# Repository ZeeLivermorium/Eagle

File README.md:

# Eagle Libraries And Projects

Some of my custom Eagle libraries and projects that are probably worth sharing.

- See [libraries](libraries) folder for libraries.
- See [projects](projects) folder for projects.

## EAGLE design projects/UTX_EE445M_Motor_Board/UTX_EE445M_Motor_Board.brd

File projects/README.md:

# Eagle Projects
Some of my Eagle project files.

## [ESP8266 Programmer](ESP8266_Programmer)
A firmware programmer of ESP8266-01 wifi module. You can also use it for serial input for your ESP8266.

## [NFC Demo Board - PN532 - TM4C123GXL](LiDAR_Demo_Board-VL53L0X-TM4C123G)
A demo board for NFC functionality demo, utilizing NXP PN532 NXP Controller and TI TM4C123GXL MCU.

## [LiDAR Demo Board - VL53L0X - TM4C123GXL](LiDAR_Demo_Board_Vert-VL53L0X-TM4C123G)
A demo board for STMicroeletronics VL53L0X ToF LiDAR sensor with TI TM4C123GXL MCU.

## [LiDAR Demo Board Vertical - VL53L0X - TM4C123GXL](NFC_Demo_Board-PN532-TM4C123G)
Another version of the LiDAR demo board with the LiDAR sensor standing vertically.

## [UTexas EE445M Front LiDAR Board Version 1](UTX_EE445M_Front_LiDAR_Board_1)
A PCB for holding front LiDAR sensors for UTexas EE445M autonomous driving car.

## [UTexas EE445M Front LiDAR Board Version 2](UTX_EE445M_Front_LiDAR_Board_2)
Another version of LiDAR front board for easier custom placement for LiDAR sensors.

## [ICDI Debugger Bridge](ICDI_Bridge)
A tiny ICDI debugger bridge to debug Tiva MCUs for custom designs.

## [Raspberry Pi Bridge](Raspberry_Pi_Bridge)
A bridge to interface raspberry pi with custom PCBs.

## [LM2596S Buck Converter Reference Board](Buck_Converter_Reference_Board_5V_3A_LM2596S)
A buck converter reference design for LM2596S.

## [UTexas EE445M Sensor Board](UTX_EE445M_Sensor_Board)
My custom sensor board design for my autonomous driving car for UTexas EE445M.

## [UTexas EE445M Motor Board](UTX_EE445M_Motor_Board)
My custom motor board design for my autonomous driving car for UTexas EE445M.

## Copyright Note
Some of the projects here contain Texas Longhorns or UT ECE logos. Those are properties of University of Texas at Austin. Any PCBs that I put those logos on are purely for academic use at UT ECE. If you download my designs from this repo for your personal use, you might want to remove these logos in case UT lawyers call you up to have a cup of tea.

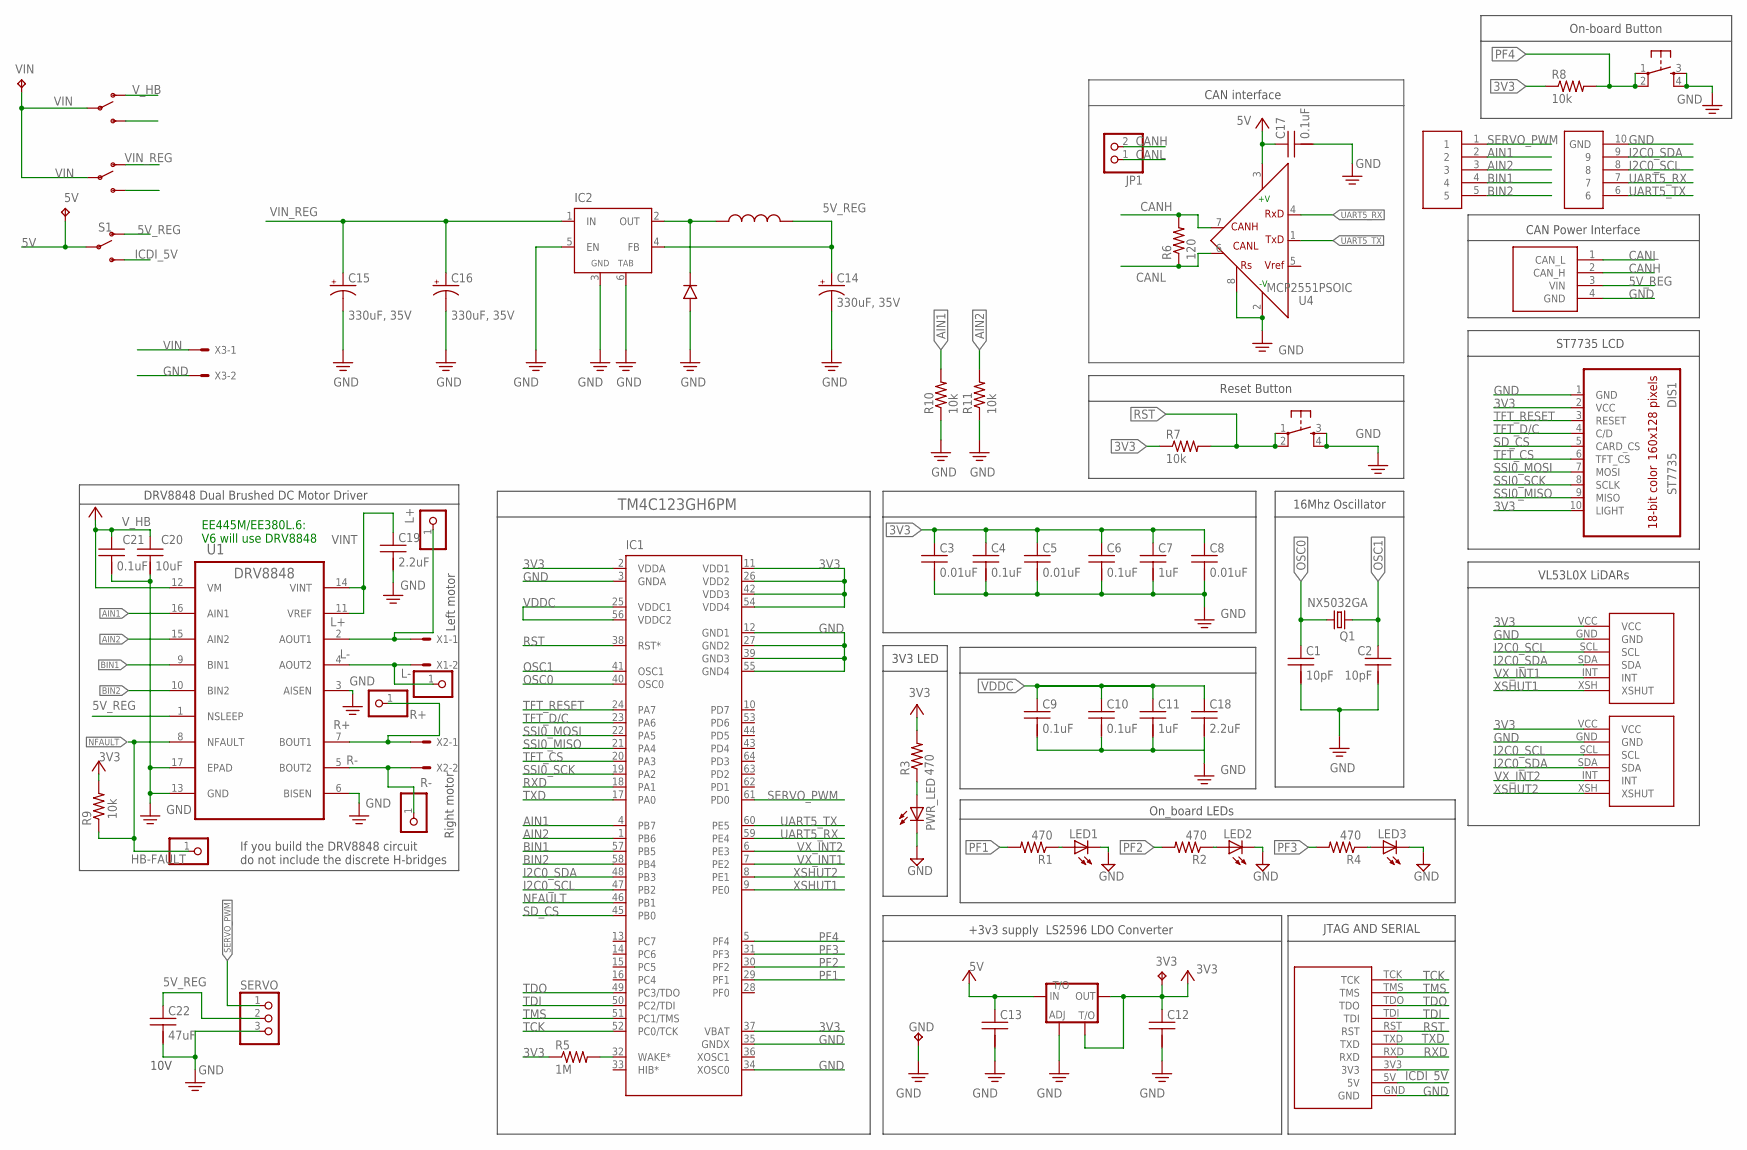
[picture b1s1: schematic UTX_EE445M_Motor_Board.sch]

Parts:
3V3, 5V: TPPAD1-13; P1-13
BUTTON: _SWITCH_DTSM-6
C1, C2: 10pF; C0603K
C3, C5, C8: 0.01uF; C0603K
C4, C6, C9, C10, C17, C21: 0.1uF; C0603K
C7, C11: 1uF; C0603K
C12: CAPACITORC0805K; C0805K
C13: CAPACITORC0603K; C0603K
C14, C15, C16: 330uF, 35V; _CAPACITOR_CHEMI-CON_A_HA0_SMD
C18, C19: 2.2uF; C0603K
C20: 10uF; C0805K
C22: 47uF; C0805K
DIS1: ST7735
GND: TPPAD1-13; P1-13
HB-FAULT: PINHD-1X1; 1X01
IC1: TM4C123GH6PM; SQFP-S-10X10-64
IC2: _VOLTAG_REGULATOR_LM2596S; _PACKAGE_TO263-5
JP1: PINHD-1X2; 1X02
L+: PINHD-1X1; 1X01
L-: PINHD-1X1; 1X01
LED1, LED2, LED3: LEDCHIP-LED0603; CHIP-LED0603
PWR_LED: LEDCHIP-LED0603; CHIP-LED0603
Q1: NX5032GA
R1, R2, R3, R4: 470; R0603
R5: 1M; R0603
R6: 120; R0603
R7, R8, R9, R10, R11: 10k; R0603
R+: PINHD-1X1; 1X01
R-: PINHD-1X1; 1X01
RESET: _SWITCH_DTSM-6
S1: SWITCH-SPDT-PTH-11.6X4.0MM; SWITCH_SPDT_PTH_11.6X4.0MM
SERVO: PINHD-1X3; 1X03
U1: DRV8848; SOP65P640X120-17N
U4: MCP2551PSOIC; SO08
U$1: JTAG_SERIAL; JTAG_SERIAL_PTH
U$2, U$3: LIDAR_VL53L0X_ATK_VERT
U$4, U$5: _SWITCH_SPDT_4.7
U$9: _VOLTAGE_REGULATOR_AMS1117; _PACKAGE_SOT223
U$10: UTX_EE445M_BOARD_CONNECTOR; _HEADER_2_4X1_ANGLED
U$11: LOGIC_ANALYZER_10PIN
U$23: _INDUCTOR_PE-54040SNL; _PACKAGE_HCI-68
U$24: _DIODE_SOD128; _PACKAGE_SOD128
VIN: TPPAD1-13; P1-13
X1, X2, X3: KK-156-2

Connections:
3V3: 3V3.TP, C3.1, C4.1, C5.1, C6.1, C7.1, C8.1, C12.1, DIS1.2 (VCC), DIS1.10 (LIGHT), IC1.2 (VDDA), IC1.11 (VDD1), IC1.26 (VDD2), IC1.37 (VBAT), IC1.42 (VDD3), IC1.54 (VDD4), R3.2, R5.1, R7.1, R8.1, R9.2, U$2.VCC, U$3.VCC, U$9.2 (OUT), U$9.4 (T/O)
5V: 5V.TP, C13.1, C17.1, S1.2, U4.3 (VDD), U$9.3 (IN)
5V_REG: C14.+, C22.1, IC2.4 (FB), S1.1 (O), SERVO.2, U1.1 (NSLEEP), U$10.3 (VIN), U$23.2
AIN1: IC1.4 (PB7), R10.2, U1.16 (AIN1), U$11.2
AIN2: IC1.1 (PB6), R11.2, U1.15 (AIN2), U$11.3
BIN1: IC1.57 (PB5), U1.9 (BIN1), U$11.4
BIN2: IC1.58 (PB4), U1.10 (BIN2), U$11.5
CANH: JP1.2, R6.2, U4.7 (CANH), U$10.2 (CAN_H)
CANL: JP1.1, R6.1, U4.6 (CANL), U$10.1 (CAN_L)
GND: BUTTON.3, BUTTON.4, C1.2, C2.2, C3.2, C4.2, C5.2, C6.2, C7.2, C8.2, C9.2, C10.2, C11.2, C12.2, C13.2, C14.-, C15.-, C16.-, C17.2, C18.2, C19.2, C20.2, C21.2, C22.2, DIS1.1 (GND), GND.TP, IC1.3 (GNDA), IC1.12 (GND1), IC1.27 (GND2), IC1.34 (XOSC0), IC1.35 (GNDX), IC1.39 (GND3), IC1.55 (GND4), IC2.3 (GND), IC2.5 (EN), IC2.6 (TAB), LED1.C, LED2.C, LED3.C, PWR_LED.C, R10.1, R11.1, RESET.3, RESET.4, SERVO.3, U1.3 (AISEN), U1.6 (BISEN), U1.13 (GND), U1.17 (EPAD), U4.2 (VSS), U4.8 (RS), U$1.GND, U$2.GND, U$3.GND, U$9.1 (ADJ), U$10.4 (GND), U$11.10 (GND), U$24.A (+), X3.2
I2C0_SCL: IC1.47 (PB2), U$2.SCL, U$3.SCL, U$11.8
I2C0_SDA: IC1.48 (PB3), U$2.SDA, U$3.SDA, U$11.9
ICDI_5V: S1.3 (S), U$1.5V
L+: L+.1, U1.2 (AOUT1), X1.1
L-: L-.1, U1.4 (AOUT2), X1.2
unnamed: LED1.A, R1.1
unnamed: PWR_LED.A, R3.1
unnamed: LED2.A, R2.1
unnamed: LED3.A, R4.1
unnamed: IC2.2 (OUT), U$23.1, U$24.C (-)
unnamed: IC1.32 (WAKE*), R5.2
NFAULT: HB-FAULT.1, IC1.46 (PB1), R9.1, U1.8 (NFAULT)
OSC0: C1.1, IC1.40 (OSC0), Q1.1
OSC1: C2.1, IC1.41 (OSC1), Q1.2
PF1: IC1.29 (PF1), R1.2
PF2: IC1.30 (PF2), R2.2
PF3: IC1.31 (PF3), R4.2
PF4: BUTTON.1, BUTTON.2, IC1.5 (PF4), R8.2
R+: R+.1, U1.7 (BOUT1), X2.1
R-: R-.1, U1.5 (BOUT2), X2.2
RST: IC1.38 (RST*), R7.2, RESET.1, RESET.2, U$1.RST
RXD: IC1.18 (PA1), U$1.RXD
SD_CS: DIS1.5 (CARD_CS), IC1.45 (PB0)
SERVO_PWM: IC1.61 (PD0), SERVO.1, U$11.1
SSI0_MISO: DIS1.9 (MISO), IC1.21 (PA4)
SSI0_MOSI: DIS1.7 (MOSI), IC1.22 (PA5)
SSI0_SCK: DIS1.8 (SCLK), IC1.19 (PA2)
TCK: IC1.52 (PC0/TCK), U$1.TCK
TDI: IC1.50 (PC2/TDI), U$1.TDI
TDO: IC1.49 (PC3/TDO), U$1.TDO
TFT_CS: DIS1.6 (TFT_CS), IC1.20 (PA3)
TFT_D/C: DIS1.4 (C/D), IC1.23 (PA6)
TFT_RESET: DIS1.3 (RESET), IC1.24 (PA7)
TMS: IC1.51 (PC1/TMS), U$1.TMS
TXD: IC1.17 (PA0), U$1.TXD
UART5_RX: IC1.59 (PE4), U4.4 (RXD), U$11.7
UART5_TX: IC1.60 (PE5), U4.1 (TXD), U$11.6
VDDC: C9.1, C10.1, C11.1, C18.1, IC1.25 (VDDC1), IC1.56 (VDDC2)
VIN: U$4.P$2, U$5.P$2, VIN.TP, X3.1
VINT: C19.1, U1.11 (VREF), U1.14 (VINT)
VIN_REG: C15.+, C16.+, IC2.1 (IN), U$5.P$1 (O)
VX_INT1: IC1.7 (PE2), U$2.INT
VX_INT2: IC1.6 (PE3), U$3.INT
V_HB: C20.1, C21.1, U1.12 (VM), U$4.P$1 (O)
XSHUT1: IC1.9 (PE0), U$2.XSH (XSHUT)
XSHUT2: IC1.8 (PE1), U$3.XSH (XSHUT)

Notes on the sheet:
16Mhz Oscillator
ST7735 LCD
VL53L0X LiDARs
CAN interface
+3v3 supply LS2596 LDO Converter
JTAG AND SERIAL
3V3 LED
On_board LEDs
Reset Button
CAN Power Interface
On-board Button
Left motor
Right motor
DRV8848 Dual Brushed DC Motor Driver
If you build the DRV8848 circuit do not include the discrete H-bridges
EE445M/EE380L.6: V6 will use DRV8848
10V

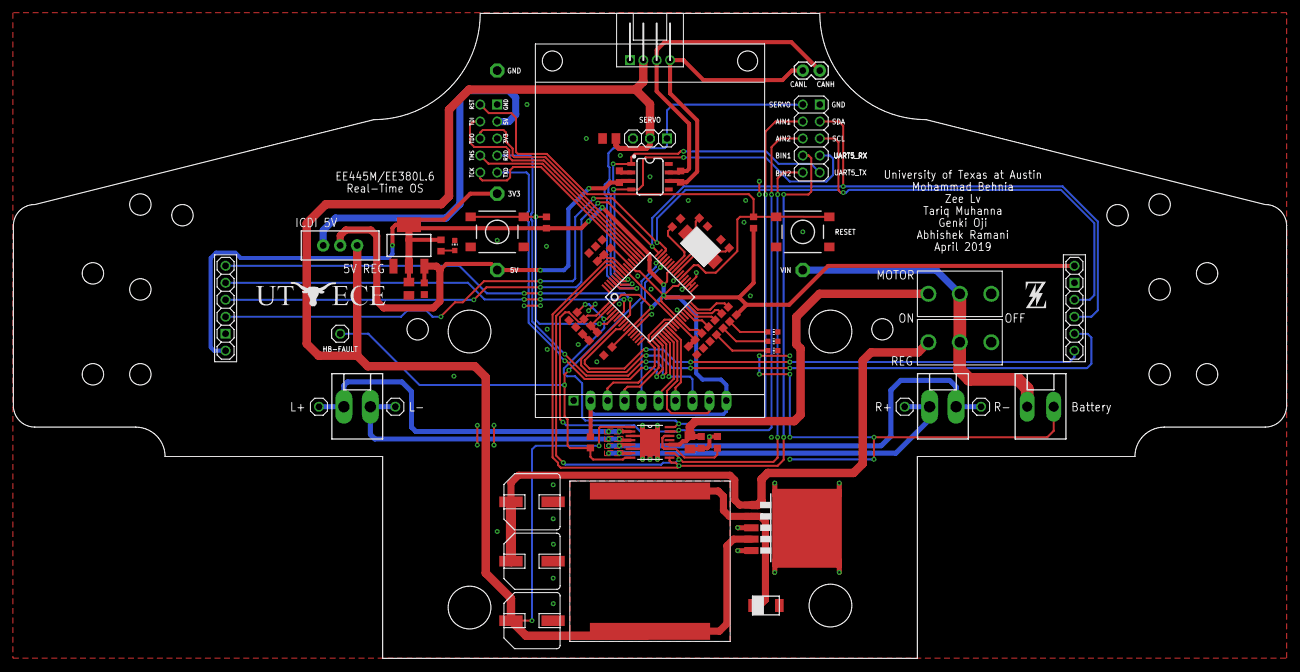
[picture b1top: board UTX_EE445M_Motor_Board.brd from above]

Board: 2 copper layers, 190.5 x 96.5 mm, 72 parts (0 on the bottom side), 56 nets.

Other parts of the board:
U$6: __LOGO_UT_ECE
U$7: __LOGO_Z

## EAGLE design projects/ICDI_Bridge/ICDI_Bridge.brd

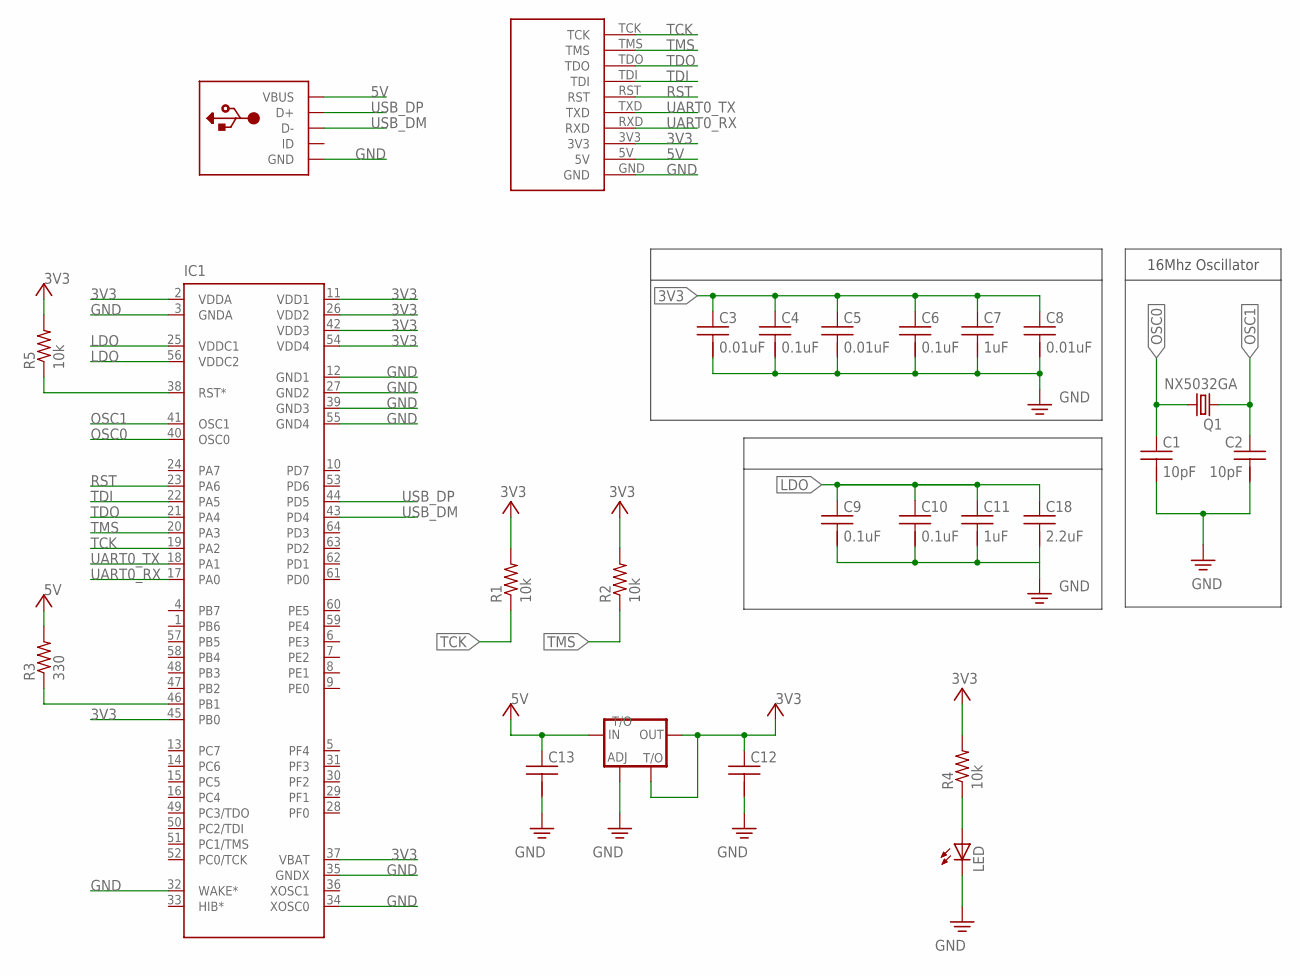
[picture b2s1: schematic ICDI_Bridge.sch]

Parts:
C1, C2: 10pF; C0603K
C3, C5, C8: 0.01uF; C0603K
C4, C6, C9, C10: 0.1uF; C0603K
C7, C11: 1uF; C0603K
C12: CAPACITORC0805K; C0805K
C13: CAPACITORC0603K; C0603K
C18: 2.2uF; C0603K
IC1: TM4C123GH6PM; SQFP-S-10X10-64
LED: LEDCHIPLED_0603; CHIPLED_0603
Q1: NX5032GA
R1, R2, R4, R5: 10k; R0603
R3: 330; R0603
U$1: USB_MICRO_PTH
U$2: JTAG_SERIAL; JTAG_SERIAL_PTH
U$4: _VOLTAGE_REGULATOR_AMS1117; _PACKAGE_SOT223

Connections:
3V3: C3.1, C4.1, C5.1, C6.1, C7.1, C8.1, C12.1, IC1.2 (VDDA), IC1.11 (VDD1), IC1.26 (VDD2), IC1.37 (VBAT), IC1.42 (VDD3), IC1.45 (PB0), IC1.54 (VDD4), R1.2, R2.2, R4.2, R5.2, U$2.3V3, U$4.2 (OUT), U$4.4 (T/O)
5V: C13.1, R3.2, U$1.1 (VBUS), U$2.5V, U$4.3 (IN)
GND: C1.2, C2.2, C3.2, C4.2, C5.2, C6.2, C7.2, C8.2, C9.2, C10.2, C11.2, C12.2, C13.2, C18.2, IC1.3 (GNDA), IC1.12 (GND1), IC1.27 (GND2), IC1.32 (WAKE*), IC1.34 (XOSC0), IC1.35 (GNDX), IC1.39 (GND3), IC1.55 (GND4), LED.C, U$1.5 (GND), U$2.GND, U$4.1 (ADJ)
LDO: C9.1, C10.1, C11.1, C18.1, IC1.25 (VDDC1), IC1.56 (VDDC2)
unnamed: LED.A, R4.1
unnamed: IC1.46 (PB1), R3.1
unnamed: IC1.38 (RST*), R5.1
OSC0: C1.1, IC1.40 (OSC0), Q1.1
OSC1: C2.1, IC1.41 (OSC1), Q1.2
RST: IC1.23 (PA6), U$2.RST
TCK: IC1.19 (PA2), R1.1, U$2.TCK
TDI: IC1.22 (PA5), U$2.TDI
TDO: IC1.21 (PA4), U$2.TDO
TMS: IC1.20 (PA3), R2.1, U$2.TMS
UART0_RX: IC1.17 (PA0), U$2.RXD
UART0_TX: IC1.18 (PA1), U$2.TXD
USB_DM: IC1.43 (PD4), U$1.2 (D-)
USB_DP: IC1.44 (PD5), U$1.3 (D+)

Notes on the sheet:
16Mhz Oscillator

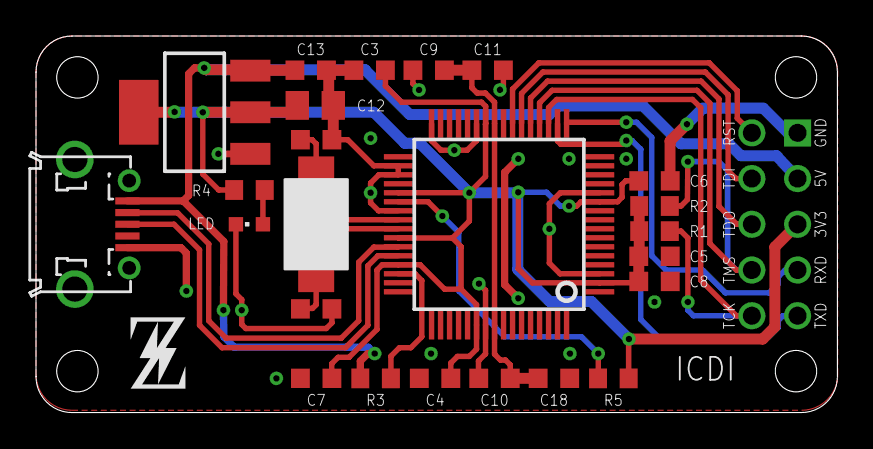
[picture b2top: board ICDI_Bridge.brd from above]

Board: 2 copper layers, 44.5 x 20.9 mm, 26 parts (0 on the bottom side), 18 nets.

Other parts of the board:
U$3: __LOGO_Z

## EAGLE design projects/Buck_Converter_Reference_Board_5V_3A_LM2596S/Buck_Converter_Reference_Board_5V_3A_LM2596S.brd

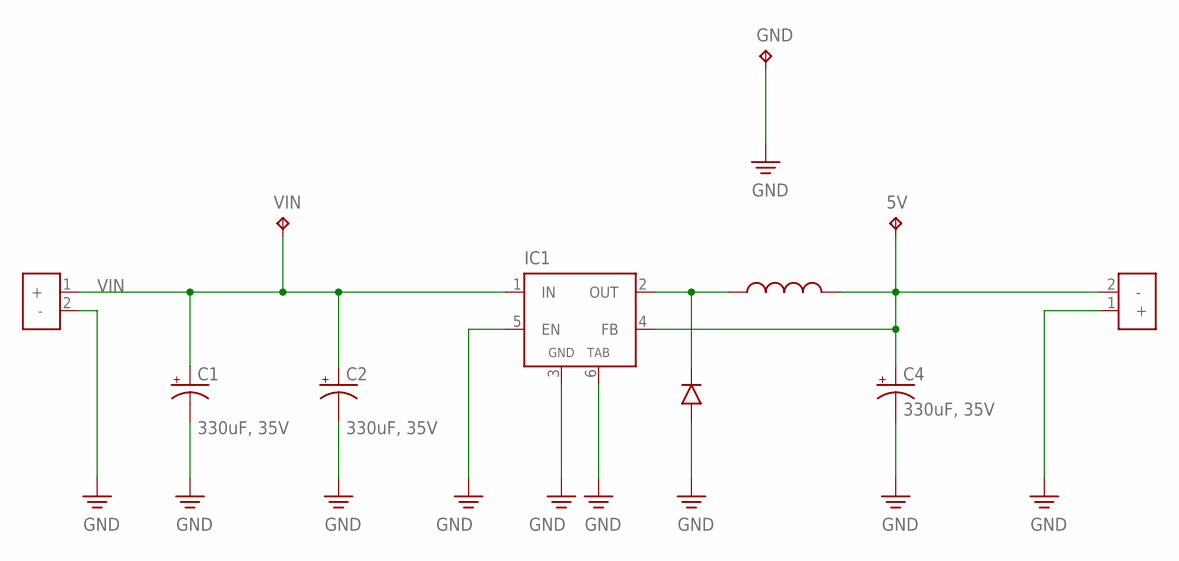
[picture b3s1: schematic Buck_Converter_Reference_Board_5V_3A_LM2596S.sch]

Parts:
5V: TPPAD1-13; P1-13
C1, C2, C4: 330uF, 35V; _CAPACITOR_CHEMI-CON_A_HA0_SMD
GND: TPPAD1-13; P1-13
IC1: _VOLTAG_REGULATOR_LM2596S; _PACKAGE_TO263-5
U$1, U$22: POWER_CONNECTOR; _TERMINAL_BLOCK_2.54_1X2
U$23: _INDUCTOR_PE-54040SNL; _PACKAGE_HCI-68
U$24: _DIODE_SOD128; _PACKAGE_SOD128
VIN: TPPAD1-13; P1-13

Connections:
5V: 5V.TP, C4.+, IC1.4 (FB), U$1.2 (-), U$23.2
GND: C1.-, C2.-, C4.-, GND.TP, IC1.3 (GND), IC1.5 (EN), IC1.6 (TAB), U$1.1 (+), U$22.2 (-), U$24.A (+)
unnamed: IC1.2 (OUT), U$23.1, U$24.C (-)
VIN: C1.+, C2.+, IC1.1 (IN), U$22.1 (+), VIN.TP

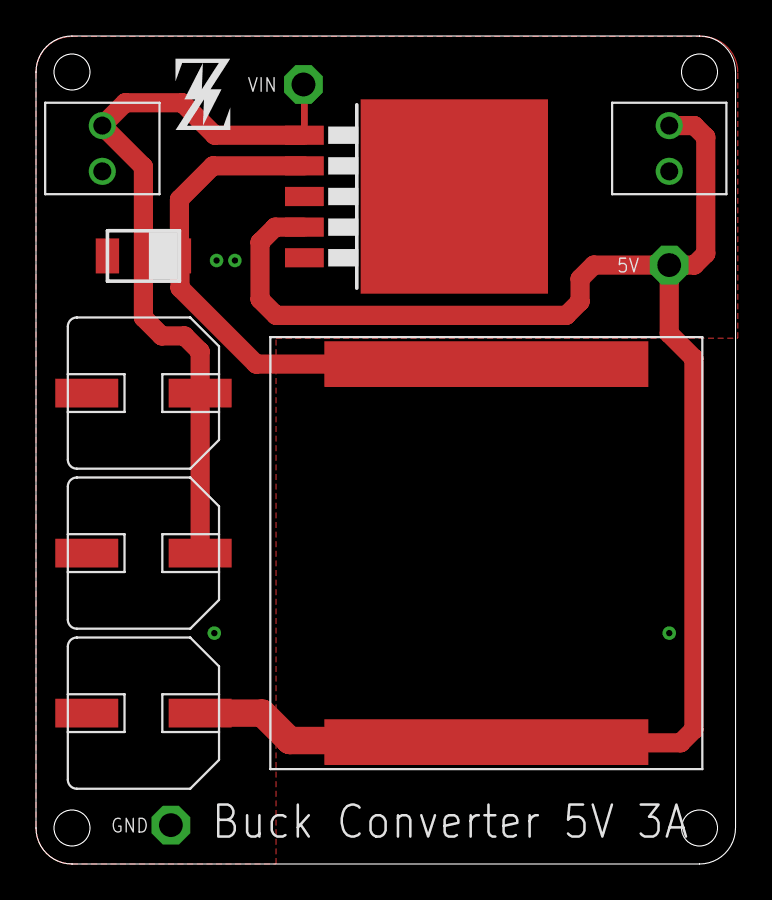
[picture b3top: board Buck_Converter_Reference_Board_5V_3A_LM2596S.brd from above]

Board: 2 copper layers, 38.9 x 46.0 mm, 12 parts (0 on the bottom side), 4 nets.

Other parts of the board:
U$2: __LOGO_Z

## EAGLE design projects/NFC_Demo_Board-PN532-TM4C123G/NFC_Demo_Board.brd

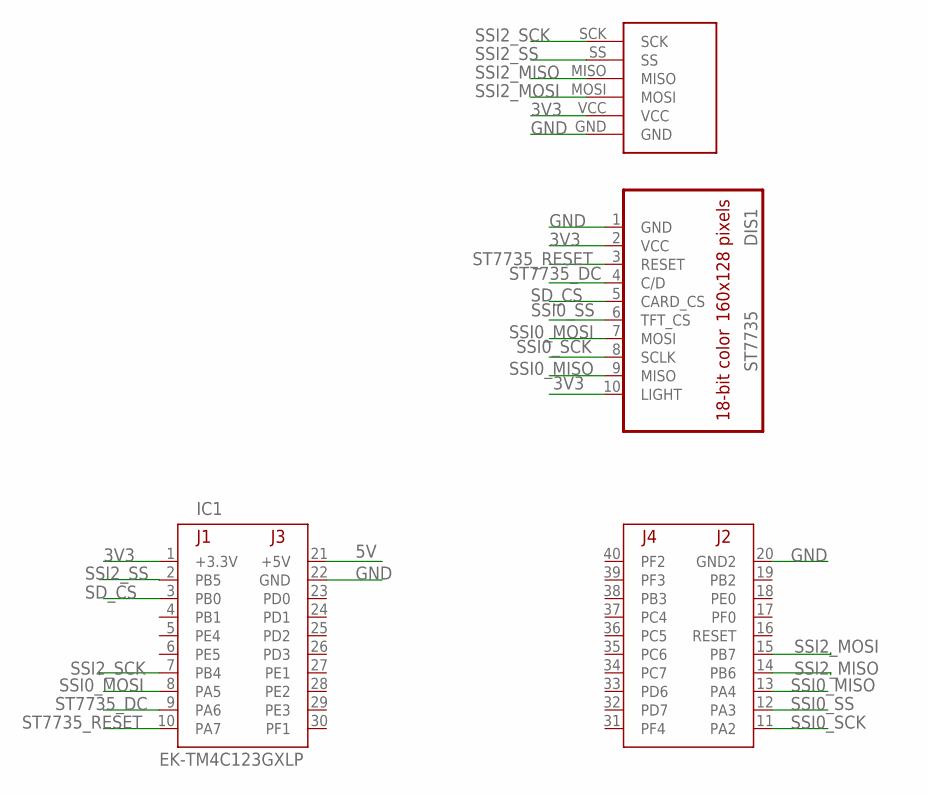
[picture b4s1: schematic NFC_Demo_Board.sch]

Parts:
DIS1: ST7735
IC1: EK-TM4C123GXLP; TM4C123LAUNCHPAD
U$1: ELECHOUSE_PN532_SPI

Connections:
3V3: DIS1.2 (VCC), DIS1.10 (LIGHT), IC1.1 (+3.3V), U$1.VCC
5V: IC1.21 (+5V)
GND: DIS1.1 (GND), IC1.20 (GND2), IC1.22 (GND), U$1.GND
SD_CS: DIS1.5 (CARD_CS), IC1.3 (PB0)
SSI0_MISO: DIS1.9 (MISO), IC1.13 (PA4)
SSI0_MOSI: DIS1.7 (MOSI), IC1.8 (PA5)
SSI0_SCK: DIS1.8 (SCLK), IC1.11 (PA2)
SSI0_SS: DIS1.6 (TFT_CS), IC1.12 (PA3)
SSI2_MISO: IC1.14 (PB6), U$1.MISO
SSI2_MOSI: IC1.15 (PB7), U$1.MOSI
SSI2_SCK: IC1.7 (PB4), U$1.SCK
SSI2_SS: IC1.2 (PB5), U$1.SS
ST7735_DC: DIS1.4 (C/D), IC1.9 (PA6)
ST7735_RESET: DIS1.3 (RESET), IC1.10 (PA7)

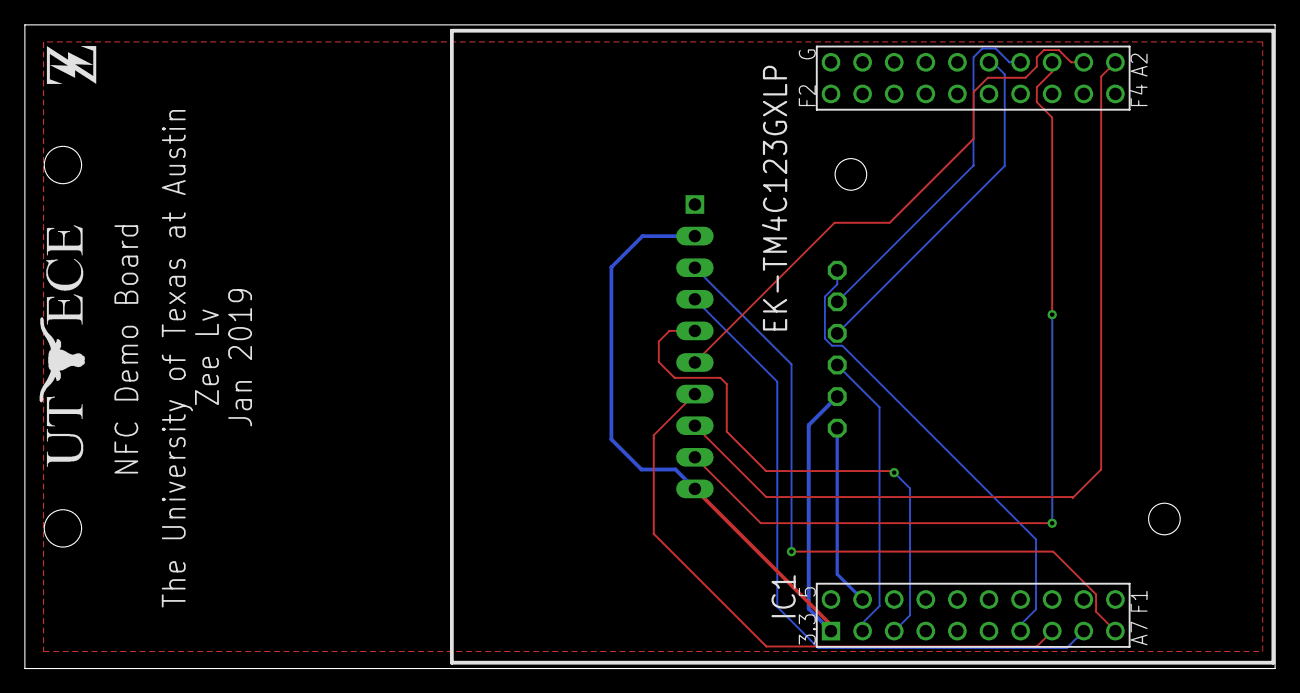
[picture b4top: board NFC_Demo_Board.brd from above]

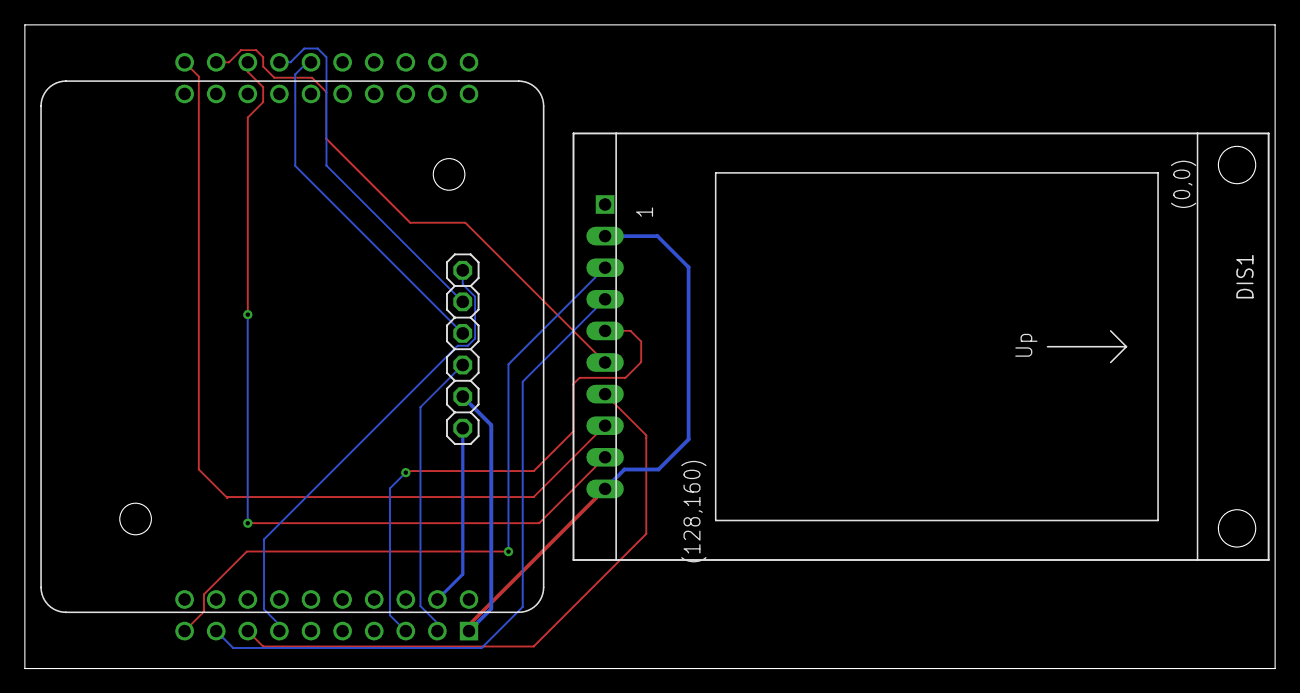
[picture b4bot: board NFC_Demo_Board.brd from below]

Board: 2 copper layers, 100.5 x 51.7 mm, 5 parts (2 on the bottom side), 13 nets.

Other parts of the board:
U$2: LOGO_UT_ECE_20X4
U$3: LOGO_Z_3X4

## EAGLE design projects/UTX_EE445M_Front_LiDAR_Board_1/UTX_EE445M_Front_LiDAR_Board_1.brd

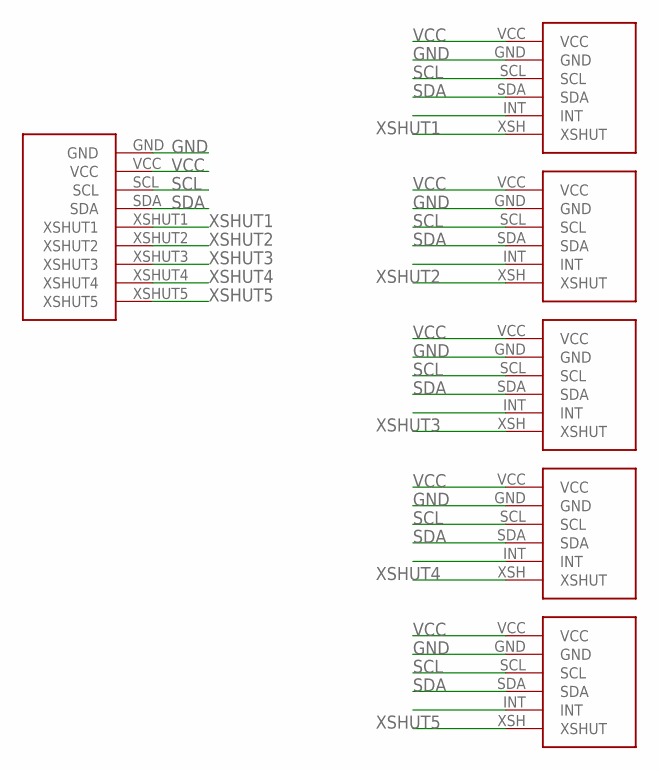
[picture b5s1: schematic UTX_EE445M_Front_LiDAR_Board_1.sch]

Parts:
U$1: UTX_EE445M_LIDAR_FRONT_BOARD_CONNECTOR_PTH
U$2, U$3, U$4, U$5, U$6: LIDAR_VL53L0X_ATK_VERT

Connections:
GND: U$1.GND, U$2.GND, U$3.GND, U$4.GND, U$5.GND, U$6.GND
SCL: U$1.SCL, U$2.SCL, U$3.SCL, U$4.SCL, U$5.SCL, U$6.SCL
SDA: U$1.SDA, U$2.SDA, U$3.SDA, U$4.SDA, U$5.SDA, U$6.SDA
VCC: U$1.VCC, U$2.VCC, U$3.VCC, U$4.VCC, U$5.VCC, U$6.VCC
XSHUT1: U$1.XSHUT1, U$2.XSH (XSHUT)
XSHUT2: U$1.XSHUT2, U$3.XSH (XSHUT)
XSHUT3: U$1.XSHUT3, U$4.XSH (XSHUT)
XSHUT4: U$1.XSHUT4, U$5.XSH (XSHUT)
XSHUT5: U$1.XSHUT5, U$6.XSH (XSHUT)

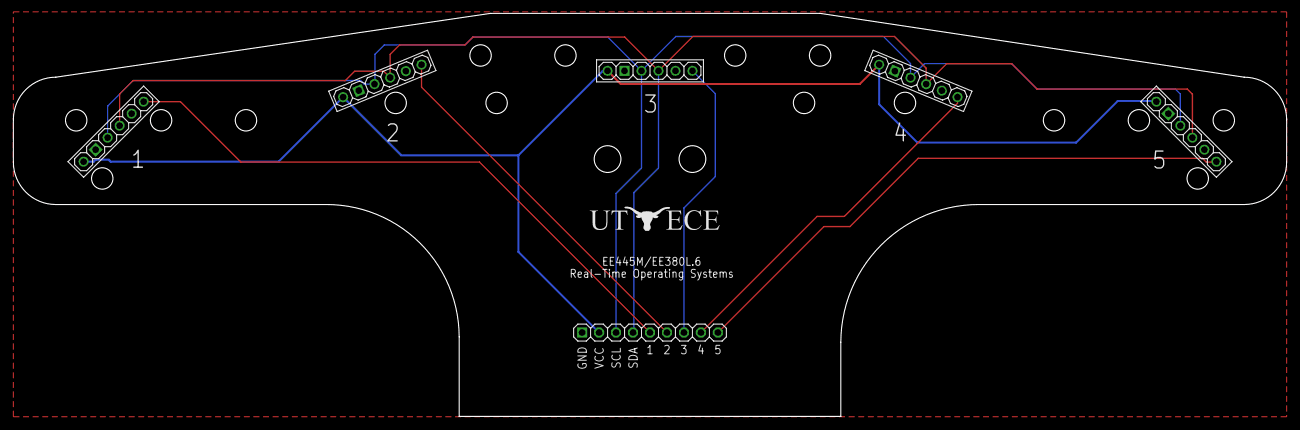
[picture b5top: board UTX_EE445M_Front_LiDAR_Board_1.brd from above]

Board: 2 copper layers, 190.5 x 60.3 mm, 8 parts (1 on the bottom side), 9 nets.

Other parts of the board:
U$7: LOGO_UT_ECE_20X4
U$8: LOGO_Z_3X4

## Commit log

2019-03-03 add 2 new designs of UTexas EE445M front LiDAR board
2019-03-03 fixed some tiny inperfections
2019-03-04 resolve lidar board file name issue
2019-04-06 April sync
2019-04-06 fix NFC demo board path, fix readme paths
2019-04-13 fix some naming and upload UTX EE445M sensor board
2019-04-23 add EE445M motor board
2019-04-23 add back lm2596s reference board
2019-06-11 add my latest designs to README
2019-06-11 fix typoe

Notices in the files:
parts and their libraries:
SparkFun-Switches: Licensing: Creative Commons ShareAlike 4.0 International - https://creativecommons.org/licenses/by-sa/4.0
